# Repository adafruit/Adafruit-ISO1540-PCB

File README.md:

## Adafruit ISO1540 Bidirectional I2C Isolator PCB

<a href="http://www.adafruit.com/products/4903"><br/>
Click here to purchase one from the Adafruit shop</a>

PCB files for the Adafruit ISO1540 Bidirectional I2C Isolator. 

Format is EagleCAD schematic and board layout
* https://www.adafruit.com/product/4903

### Description

Sometimes you'll find yourself with an I2C bus controller on one side, and an I2C bus device on the other and you gotta keep em (electrically) separated. Maybe because one is Earth-grounded, maybe because you've got some funky power monitoring setup, maybe you want to reduce noise.

Whatever it is, you can use the Adafruit ISO1540 Bidirectional I2C Isolator to add full electrical isolation between two sides of an I2C bus. The chip we use, the TI ISO1540 is fully bi-directional, supports up to 1 MHz clock rates, supports clock-stretching, works with 3 to 5V DC power or logic (separate on either side of course), with 2500 V-RMS isolation

Usage is easy - you get power/ground/clock/data breakout pads for each side as well as a matching STEMMA QT connector. Unlike our other QT boards, the two sides are obviously electrically isolated, which means each half must be powered! Check that the green LED is lit on both sides. Now send data over I2C and you're good to go. We have 10K pullups on each side, from the I2C pins to the matching VCC for that side.

For more details about chip specifications, check out the TI product page.

To get you going fast, we spun up a custom made PCB in the STEMMA QT form factor, making it easy to interface with. The STEMMA QT connectors on either side are compatible with the SparkFun Qwiic I2C connectors. This allows you to make solderless connections between your development board and the ISO1540 or to chain it with a wide range of other sensors and accessories using a compatible cable. QT Cable is not included, but we have a variety in the shop.

### License

Adafruit invests time and resources providing this open source design, please support Adafruit and open-source hardware by purchasing products from [Adafruit](https://www.adafruit.com)!

Designed by Limor Fried/Ladyada for Adafruit Industries.

Creative Commons Attribution/Share-Alike, all text above must be included in any redistribution. 
See license.txt for additional details.

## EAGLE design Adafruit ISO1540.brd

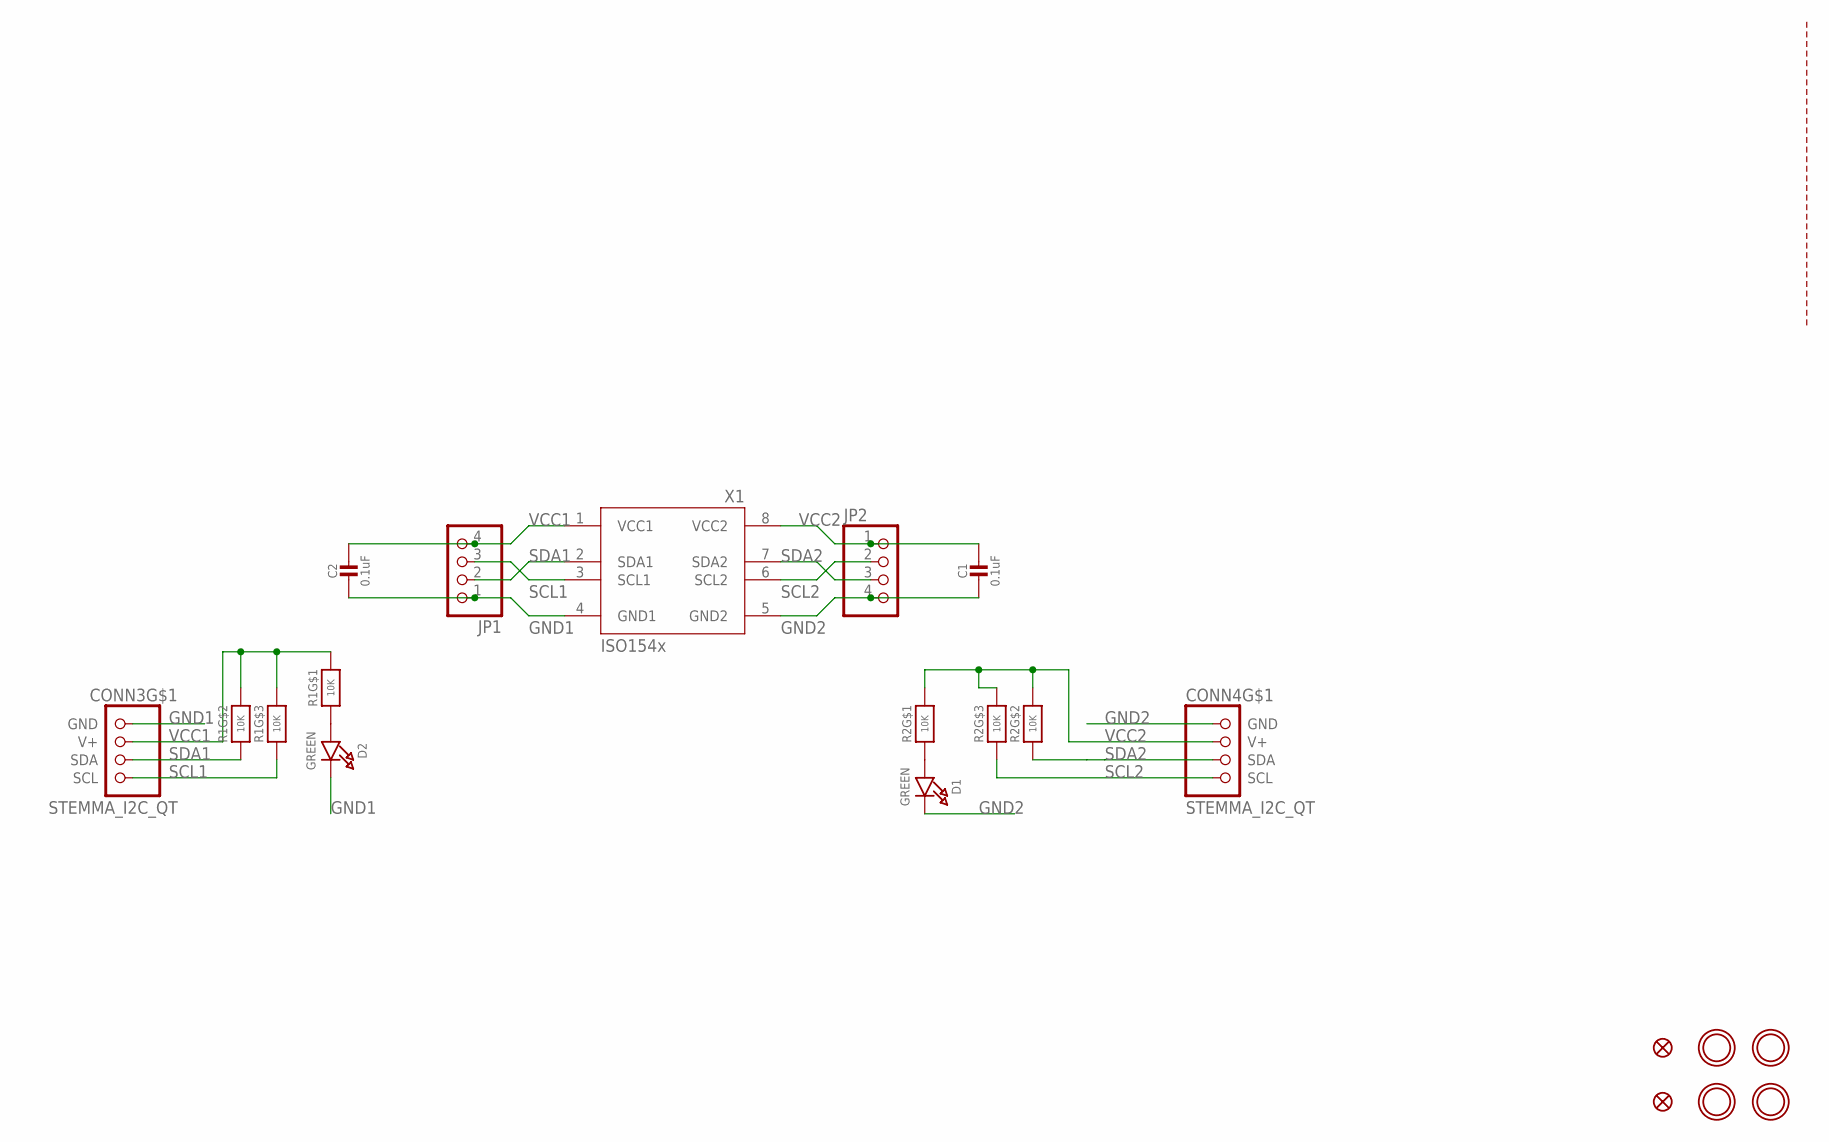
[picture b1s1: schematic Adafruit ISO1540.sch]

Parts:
C1, C2: 0.1uF; 0603-NO
CONN3, CONN4: STEMMA_I2C_QT; JST_SH4
D1, D2: GREEN; CHIPLED_0603_NOOUTLINE
FID3, FID4: FIDUCIAL_1MM
JP1, JP2: HEADER-1X4ROUND; 1X04_ROUND
R1, R2: 10K; RESPACK_4X0603
U$1, U$17, U$19, U$21: MOUNTINGHOLE2.5; MOUNTINGHOLE_2.5_PLATED
X1: ISO154X; SOIC8_150MIL

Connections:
GND1: C2.2, CONN3.1 (GND), D2.C, JP1.1, X1.4 (GND1)
GND2: C1.2, CONN4.1 (GND), D1.C, JP2.4, X1.5 (GND2)
unnamed: D2.A, R1.1
unnamed: D1.A, R2.1
SCL1: CONN3.4 (SCL), JP1.3, R1.3 (1), X1.3 (SCL1)
SCL2: CONN4.4 (SCL), JP2.2, R2.3 (1), X1.6 (SCL2)
SDA1: CONN3.3 (SDA), JP1.2, R1.2 (1), X1.2 (SDA1)
SDA2: CONN4.3 (SDA), JP2.3, R2.2 (1), X1.7 (SDA2)
VCC1: C2.1, CONN3.2 (V+), JP1.4, R1.6 (2), R1.7 (2), R1.8 (2), X1.1 (VCC1)
VCC2: C1.1, CONN4.2 (V+), JP2.1, R2.6 (2), R2.7 (2), R2.8 (2), X1.8 (VCC2)

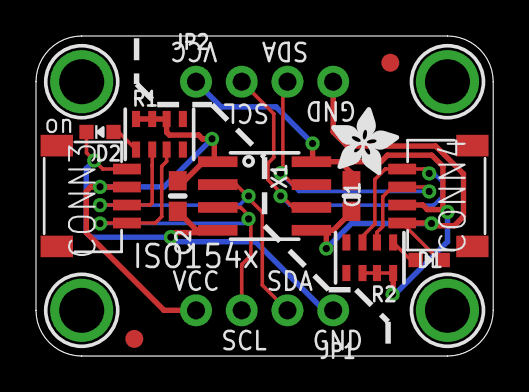
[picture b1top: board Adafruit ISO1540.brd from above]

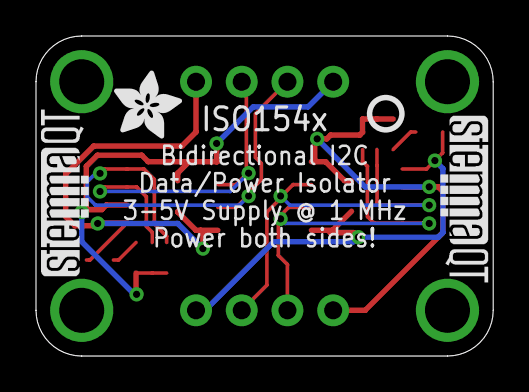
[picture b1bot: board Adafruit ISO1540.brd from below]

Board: 2 copper layers, 25.4 x 17.8 mm, 22 parts (4 on the bottom side), 10 nets.

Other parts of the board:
U$2, U$22: ADAFRUIT_3.5MM
U$25: PCBFEAT-REV-040
U$30, U$31: STEMMAQT

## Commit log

2021-02-09 adding board files.

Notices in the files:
parts and their libraries:
microbuilder: This work is placed in the public domain, and may be freely used for commercial and non-commercial work with the following conditions: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
